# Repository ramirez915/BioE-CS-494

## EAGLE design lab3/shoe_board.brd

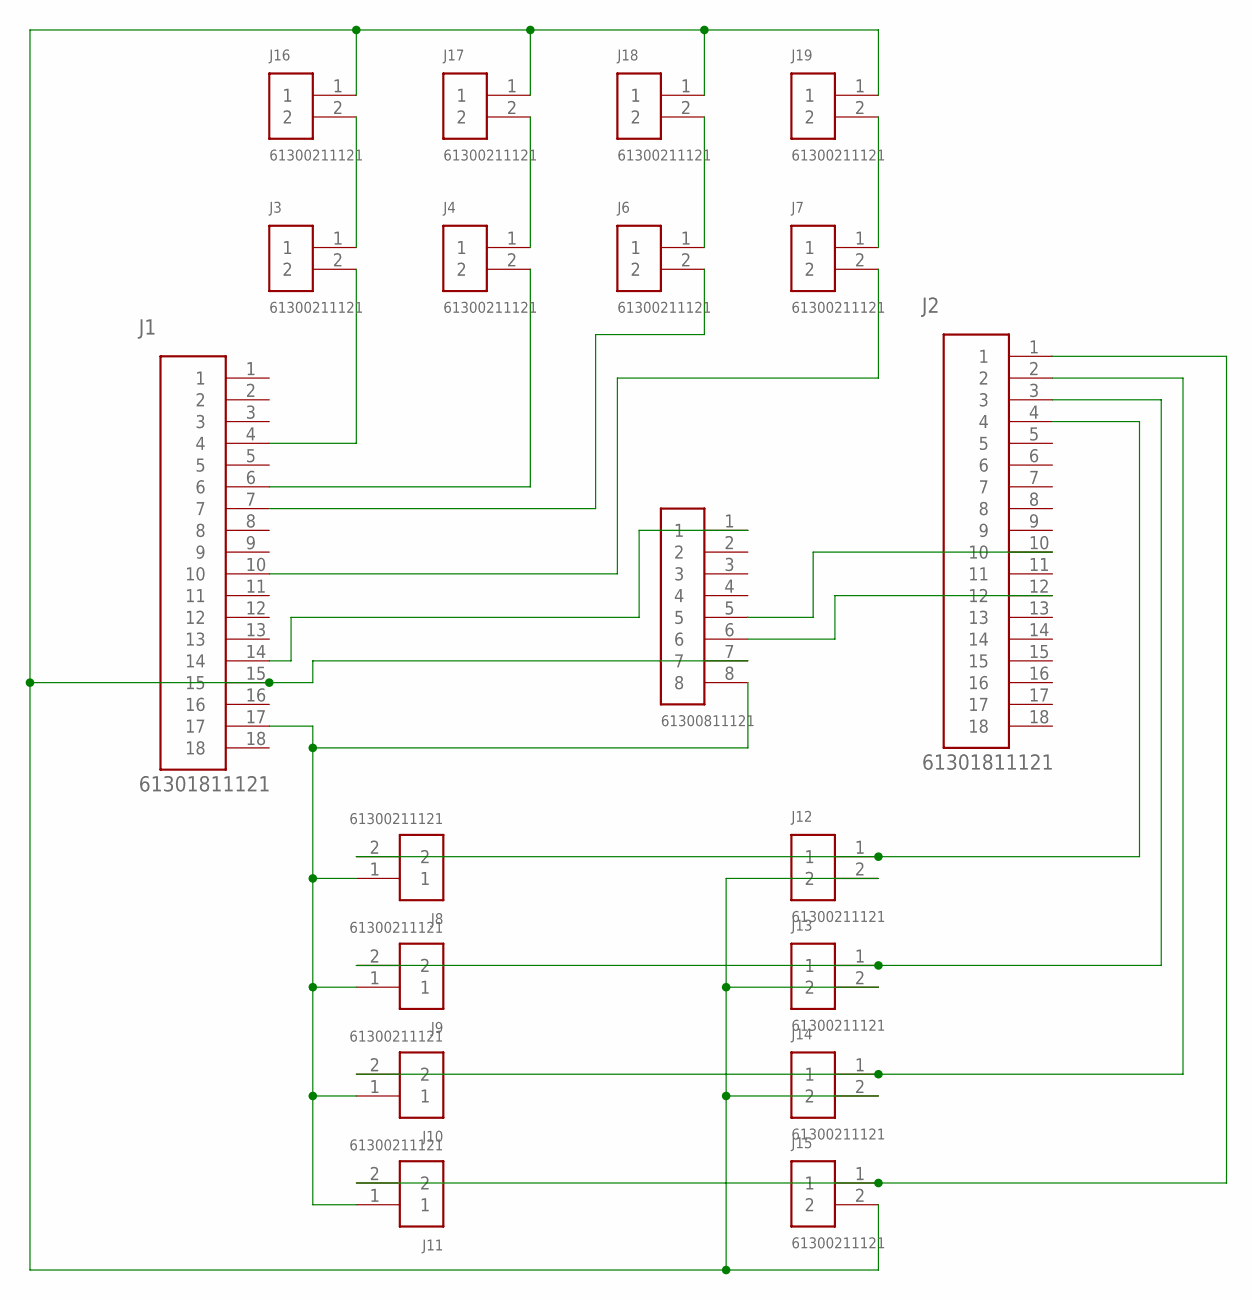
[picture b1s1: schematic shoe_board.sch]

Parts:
J1, J2: 61301811121
J3, J4, J6, J7, J8, J9, J10, J11, J12, J13, J14, J15, J16, J17, J18, J19: 61300211121
J20: 61300811121

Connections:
unnamed: J1.4, J3.2
unnamed: J1.6, J4.2
unnamed: J1.7, J6.2
unnamed: J1.10, J7.2
unnamed: J3.1, J16.2
unnamed: J4.1, J17.2
unnamed: J6.1, J18.2
unnamed: J7.1, J19.2
unnamed: J2.10, J20.5
unnamed: J1.15, J12.2, J13.2, J14.2, J15.2, J16.1, J17.1, J18.1, J19.1, J20.7
unnamed: J2.1, J11.2, J15.1
unnamed: J2.2, J10.2, J14.1
unnamed: J2.3, J9.2, J13.1
unnamed: J2.4, J8.2, J12.1
unnamed: J1.14, J20.1
unnamed: J2.12, J20.6
unnamed: J1.17, J8.1, J9.1, J10.1, J11.1, J20.8

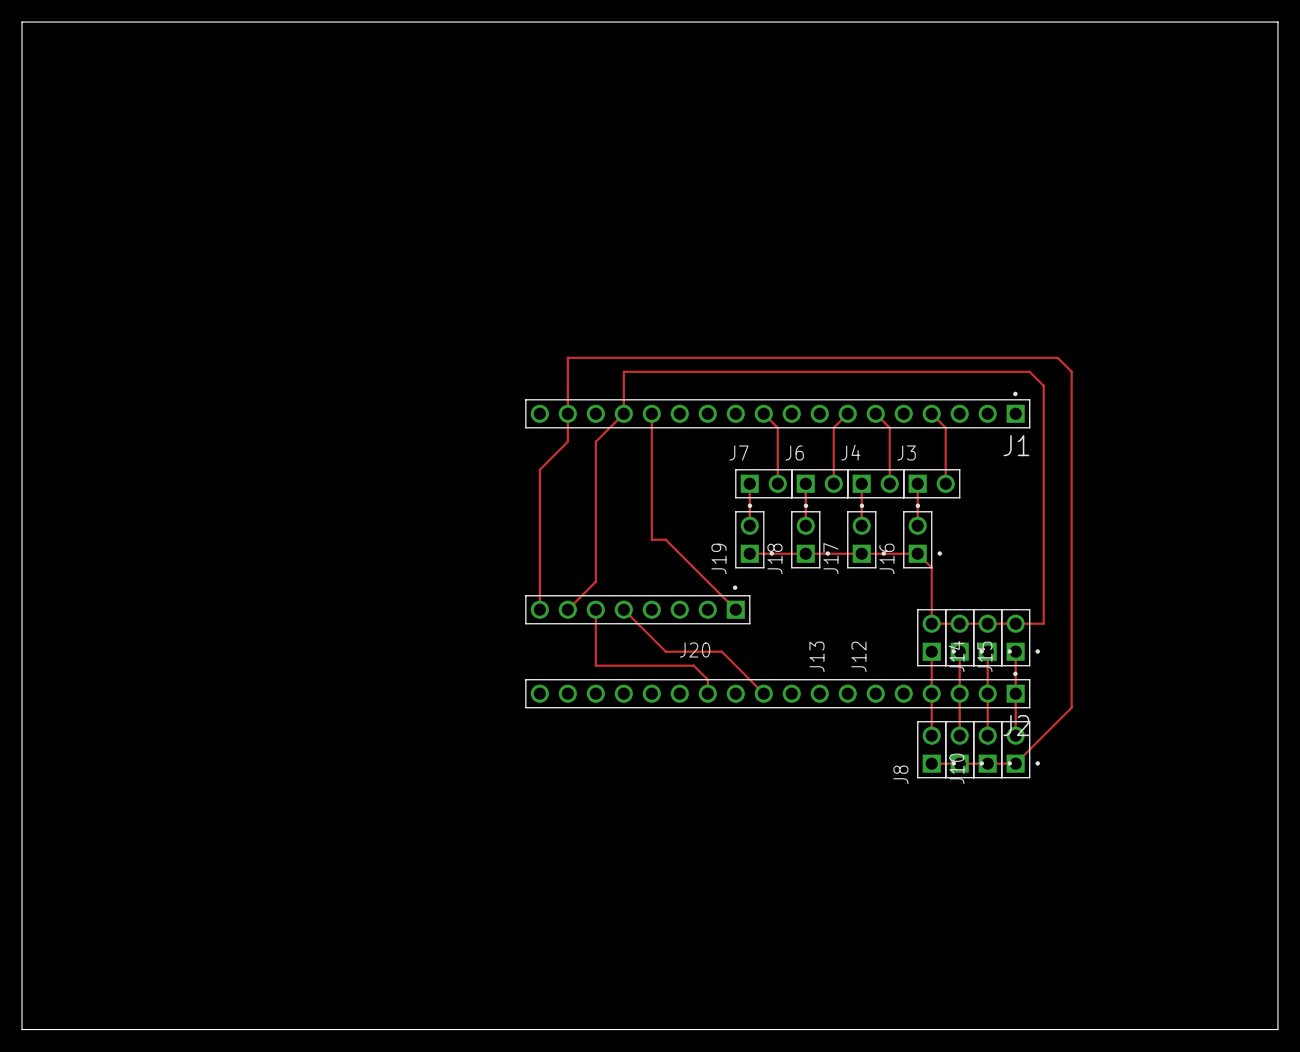
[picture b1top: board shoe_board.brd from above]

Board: 2 copper layers, 114.0 x 91.4 mm, 19 parts (0 on the bottom side), 17 nets.

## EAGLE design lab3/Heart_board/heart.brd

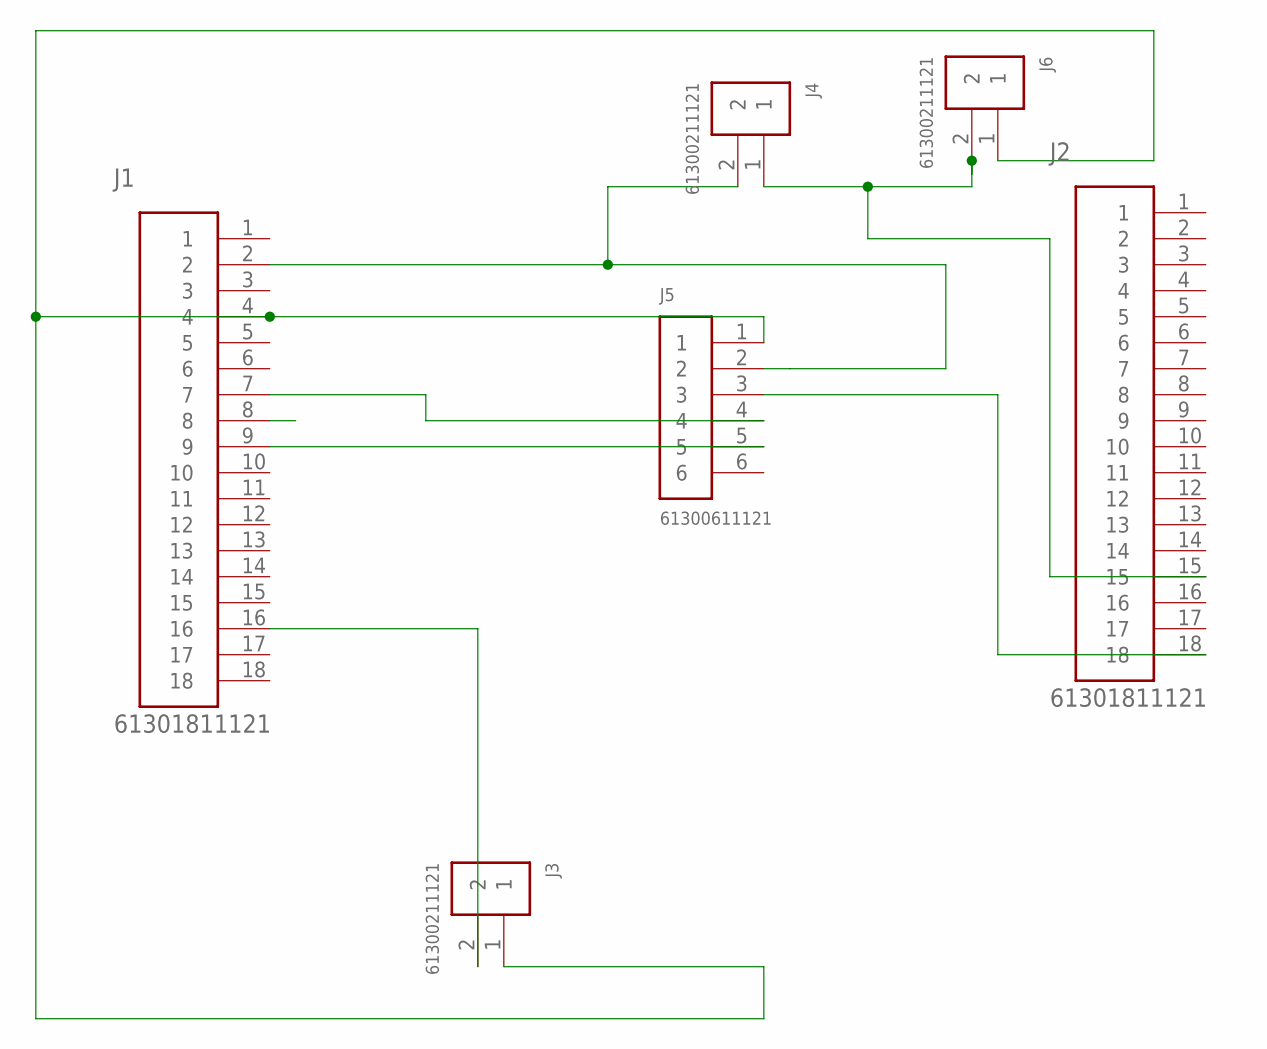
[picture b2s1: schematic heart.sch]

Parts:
J1, J2: 61301811121
J3, J4, J6: 61300211121
J5: 61300611121

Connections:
unnamed: J2.18, J5.3
unnamed: J1.2, J4.2, J5.2
unnamed: J2.15, J4.1, J6.2
unnamed: J1.9, J5.5
unnamed: J1.7, J5.4
unnamed: J1.16, J3.2
unnamed: J1.4, J3.1, J5.1, J6.1

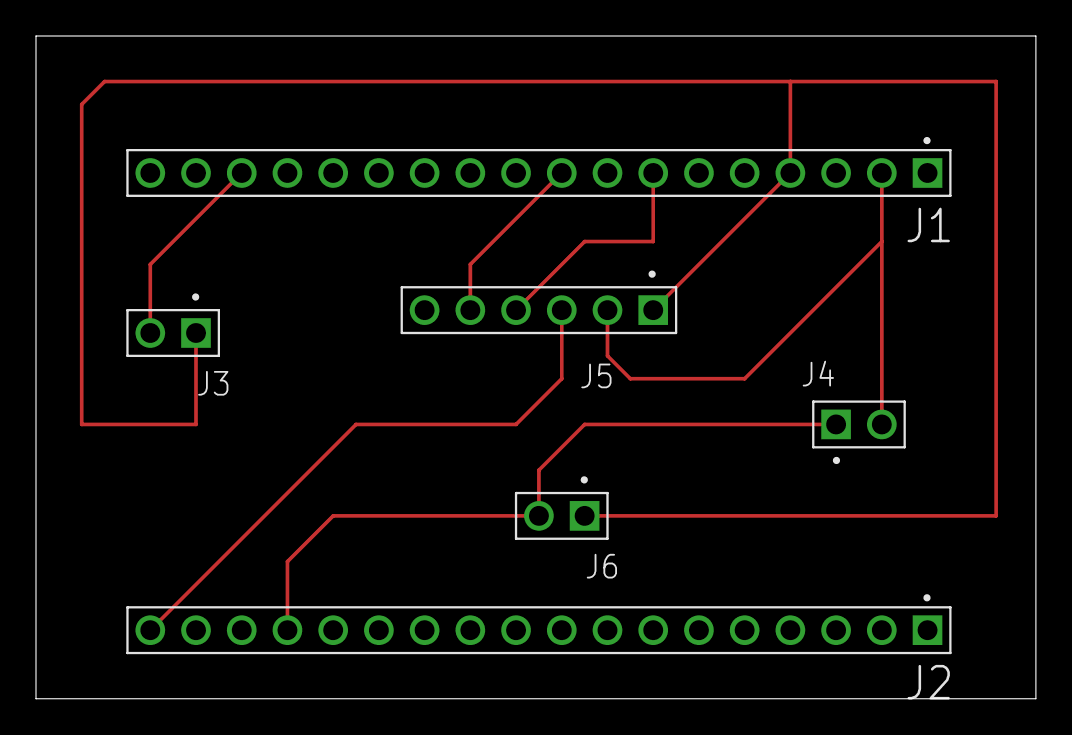
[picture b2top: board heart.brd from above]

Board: 2 copper layers, 55.5 x 36.8 mm, 6 parts (0 on the bottom side), 7 nets.

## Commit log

2019-09-24 Lab 1 files
2019-09-24 just few changes
2019-09-24 testing
2019-09-24 chabge
2019-09-25 data sends from device to processing
2019-09-25 pseudo
2019-09-25 Updated gui and arduino code
2019-09-26 UPADATE
2019-09-26 Updated fitness function
2019-09-26 signal_acquisition_update
2019-09-26 update to processing code
2019-09-26 Update lab1.ino
    update
2019-09-26 fixed code so now it compiles
2019-09-27 signal processing update
2019-09-27 test,update
2019-09-28 computing max and min
2019-09-29 buzzer code
2019-09-29 ploting two graphs
2019-09-29 Scrolls when plotting data and resets
2019-09-29 updates color and plays song
2019-09-29 commented song stuff out
    there appears to be a lag when the song code is in. May need a shorter song
2019-09-29 extra comment about song
2019-09-29 deleted song
2019-09-30 Processing code supports all modes
    All modes are now supported by processing just need to adjust code in arduino. Also would just need to modify the y axis limit maybe
2019-09-30 added my practice for processing
2019-09-30 combined and cleaned code
2019-09-30 Updated processing code
2019-10-01 lab2
2019-10-04 added new file
2019-10-04 Update lab1.ino
    wrote stress function, still needs testing and some changes but here is a rough idea.
2019-10-05 data is now properly sending to arduino
2019-10-05 working gui code
    gui works... but need to figure out how to plot the histogram nicely
2019-10-06 gui works with ALL graphs
2019-10-06 Final update for GUI and lab 1 code
    still need meditation mode
2019-10-08 set up to submit lab1
2019-10-08 last updates
2019-10-08 update to lab1_submit
2019-10-08 lab3
2019-10-15 lab3Gui
2019-10-16 image
2019-10-16 Calculate MEP function
2019-10-16 heat map working as intended
    tried getting the heat map to display 2 different sets of values but no luck...
2019-10-16 updated comments
2019-10-19 update to GUI and arduino code
2019-10-19 parsing out data from arduino
    update to gui and started parsing out data
2019-10-20 sections 2, 3 commplete
    started section 4
2019-10-20 updates to gui
2019-10-20 gui update
2019-10-21 deleted println
2019-10-21 update with section 4 from priyanka
2019-10-21 CASE
2019-10-22 updated gui
2019-10-22 upda
2019-10-22 update to gui labels
2019-10-22 update labels and created hard code gui
2019-10-22 modificatoins to lab gui copy
2019-10-22 final updates to GUIs
2019-10-22 arduino final
2019-10-24 lab3Submit
2019-10-24 Section 3 update
2019-10-24 update to lab3 added stopwatch
2019-10-24 images
2019-10-24 Arrows section 2
2019-10-25 Formatted buttond and sec 2
2019-10-25 update to section 1
    section 1 seems to be completed
2019-10-25 update to sec 4
    small fix to section 4 and 1
2019-10-27 section 1 and 4 logic complete
2019-10-28 section 1 complete with data
    need to test section 1 with firebeetle but code looks ready to go. started section 4. also started finalizing arduino code
2019-10-28 ud to connecting arduino to processing
2019-10-29 update to lab2 processing
2019-10-29 stress and meditation videos
2019-10-29 uppdated prese
2019-10-29 videos
2019-10-29 final
2019-10-29 started lab4 gui code
2019-10-29 change
2019-10-29 game
2019-10-29 push
2019-10-29 buttonslab4
2019-10-30 space invader: button size points work
2019-10-31 works with buttons
2019-11-01 comment
2019-11-02 update to print stmts for cmds
2019-11-04 added game and things work as intended
2019-11-04 lab 4 final
2019-11-05 updates to lab3 GUI and arduino code
2019-11-05 mattia presentation
2019-11-05 proessing
2019-11-05 final start
2019-11-07 changes to lab 3
2019-11-11 updates to lab 3 gui sec 4
2019-11-11 last update to lab3
2019-11-12 start to final
2019-11-12 update to final
2019-11-14 cap code updated
2019-11-14 counter boundary check function
2019-11-14 buttons
2019-11-14 update to logic
2019-11-15 updated code
2019-11-21 updated cap code. works as intended! set sensitivity now
2019-11-22 another update
2019-11-26 hardware working with software
2019-11-26 small note
2019-11-26 vocals
2019-11-30 hand images
